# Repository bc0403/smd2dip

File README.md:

# Purpose
This repository provides some SMD to DIP breakbout boards for breadboard prototype. KiCad is used for the PCB software.

##
* 0805 x2
* TSOT5, for AD8603
* SON-6C, for S-5420 UV sensor

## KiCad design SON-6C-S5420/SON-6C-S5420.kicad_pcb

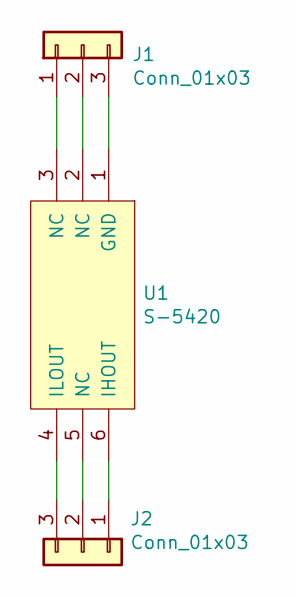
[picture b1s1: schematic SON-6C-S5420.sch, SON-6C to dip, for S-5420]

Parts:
J1, J2: Conn_01x03; PinHeader_1x03_P2.54mm_Vertical
U1: S-5420; SON-6C

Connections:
unnamed: J1.1, U1.3 (NC)
unnamed: J1.2, U1.2 (NC)
unnamed: J1.3, U1.1 (GND)
unnamed: J2.1, U1.6 (IHOUT)
unnamed: J2.2, U1.5 (NC)
unnamed: J2.3, U1.4 (ILOUT)

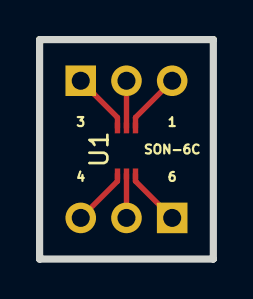
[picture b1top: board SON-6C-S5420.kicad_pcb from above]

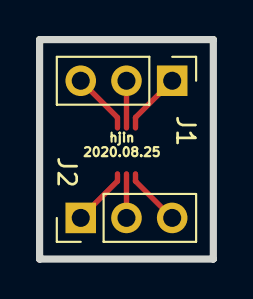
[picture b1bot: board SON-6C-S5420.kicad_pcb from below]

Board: 2 copper layers, 9.7 x 12.2 mm, 3 parts (2 on the bottom side), 6 nets.

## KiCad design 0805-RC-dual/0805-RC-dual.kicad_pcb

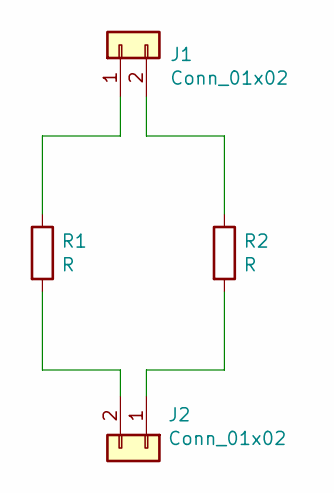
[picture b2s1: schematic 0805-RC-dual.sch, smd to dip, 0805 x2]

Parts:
J1, J2: Conn_01x02; PinHeader_1x02_P2.54mm_Vertical
R1, R2: R; R_0805_2012Metric_Pad1.15x1.40mm_HandSolder

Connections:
unnamed: J1.1, R1.1
unnamed: J1.2, R2.1
unnamed: J2.1, R2.2
unnamed: J2.2, R1.2

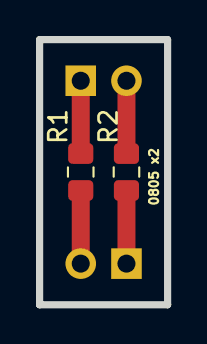
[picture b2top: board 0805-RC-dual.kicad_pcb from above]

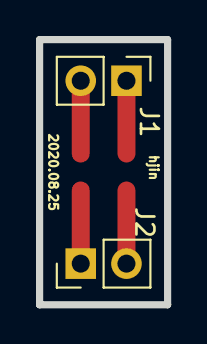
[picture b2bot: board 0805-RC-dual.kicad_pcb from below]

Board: 2 copper layers, 7.1 x 14.7 mm, 4 parts (2 on the bottom side), 4 nets.

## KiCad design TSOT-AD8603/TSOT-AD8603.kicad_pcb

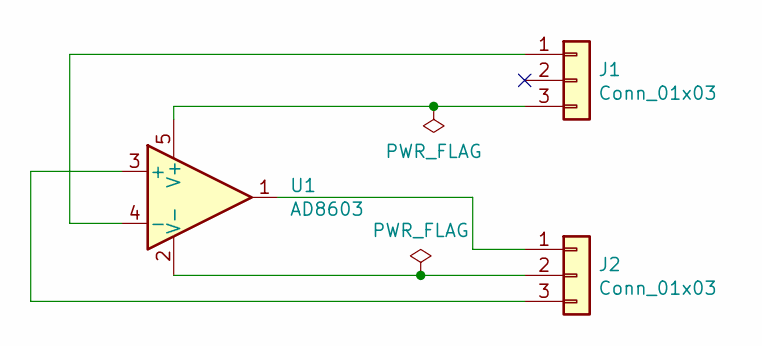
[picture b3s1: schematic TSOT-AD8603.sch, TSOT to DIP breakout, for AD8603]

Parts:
J1, J2: Conn_01x03; PinHeader_1x03_P2.54mm_Vertical
U1: AD8603; TSOT-23-5

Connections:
unnamed: J1.1, U1.4 (-)
unnamed: J1.3, U1.5 (V+)
unnamed: J2.1, U1.1
unnamed: J2.2, U1.2 (V-)
unnamed: J2.3, U1.3 (+)

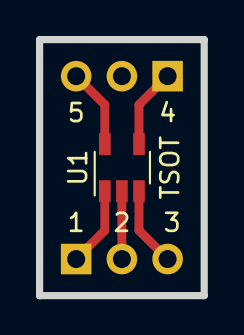
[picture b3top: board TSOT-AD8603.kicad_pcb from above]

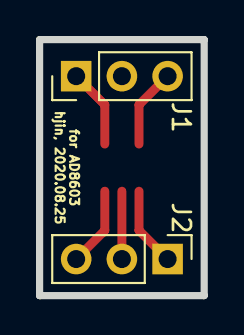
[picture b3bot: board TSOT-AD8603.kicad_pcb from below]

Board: 2 copper layers, 9.1 x 14.2 mm, 3 parts (2 on the bottom side), 5 nets.

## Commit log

2020-08-25 initial
2020-08-25 revise gitignore
